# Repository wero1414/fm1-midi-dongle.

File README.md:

# FM-1 MIDI dongle

A small stick that plugs into the M-VAVE FM-1's USB-C port and gives it a **TRS MIDI OUT** and an
**isolated TRS MIDI IN**. The FM-1 is a USB MIDI device, so the dongle is a USB host built on the
WCH **CH32X035G8U6** (the cheapest WCH part with a full-speed USB host). It works with any FM-1 firmware
that sends MIDI over USB: Melodee, SLOOP, Felucca, Hortator, stock.

- `DESIGN.md`: the locked design, verified pins, open items, firmware plan, cost.
- `BOM.csv`: parts with LCSC numbers and a *Verified* column.
- `fm1-midi-dongle.kicad_sch` / `.kicad_pro`: KiCad 10 schematic (ERC clean). Generated by `tools/gen_sch.py`.
- `fm1-midi-dongle.kicad_pcb`: the board with placement only (generated by `tools/gen_pcb.py`); routing is manual.
- `fm1_dongle.kicad_sym`, `fm1_dongle.pretty`, `fm1_dongle.3dshapes`: project symbols and the exact LCSC footprints
  (from EasyEDA) for every IC and connector. `tools/export_jlc.sh` makes the JLCPCB BOM.

Status (2026-10-17): schematic done; PCB floorplanned (20 x 26 mm, 4 layers, 0.8 mm, placement DRC clean),
routing not started; firmware not started.

## Hardware summary
- USB-C male plug to the FM-1 (host side, 56 kΩ Rp on CC), VBUS through an SY6280AAC load switch set to 1 A.
- USB-C female for 5 V in only (5.1 kΩ Rd on CC1/CC2), no data.
- MIDI OUT: 3.3 V TRS type A (10 Ω tip, 33 Ω ring), PJ-320D jacks.
- MIDI IN: H11L1SM optocoupler, 220 Ω, 1N4148 reverse diode, TRS type A.
- Programming: WCH-LinkE on three bare pads (3V3 / PC18 DIO / GND), no connector.

## License
Hardware: CERN-OHL-P-2.0 (proposed; change if you prefer).

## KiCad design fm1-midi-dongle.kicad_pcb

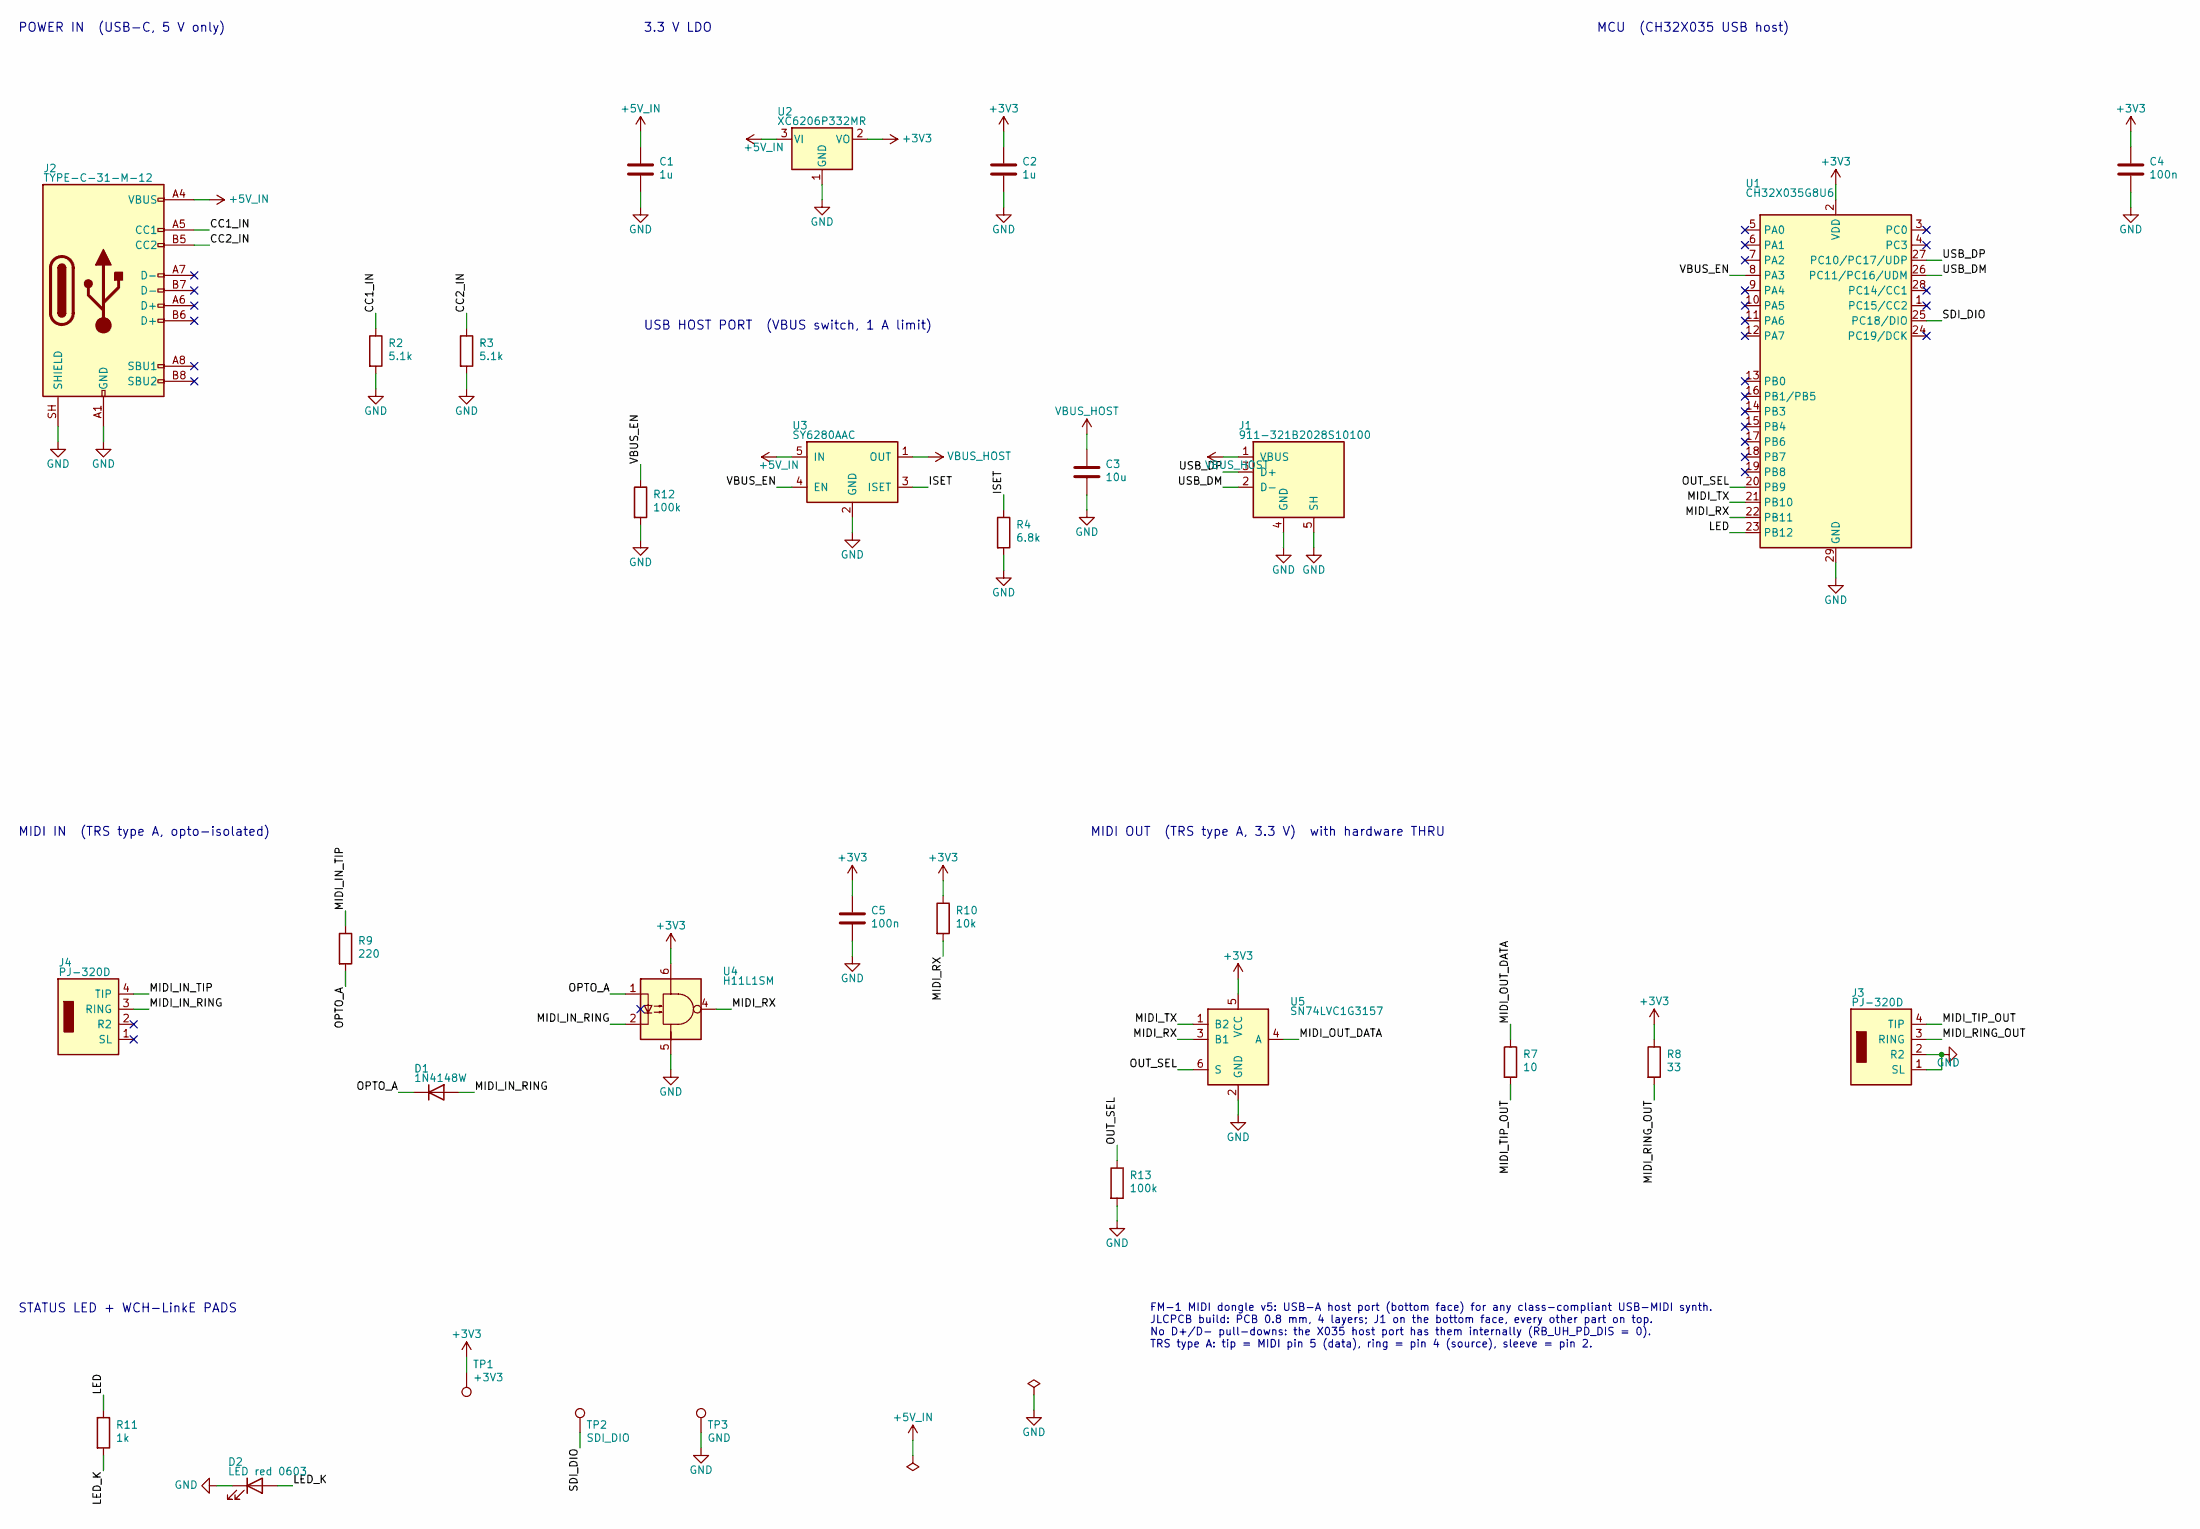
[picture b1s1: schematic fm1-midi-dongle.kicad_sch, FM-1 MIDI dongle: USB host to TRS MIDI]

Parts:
C1, C2: 1u; C_0603_1608Metric; MPN CL10A105KB8NNNC; LCSC# C15849
C3: 10u; C_0603_1608Metric; MPN CL10A106MA8NRNC; LCSC# C96446
C4, C5: 100n; C_0603_1608Metric; MPN CC0603KRX7R9BB104; LCSC# C14663
D1: 1N4148W; D_SOD-123; MPN 1N4148W; LCSC# C81598
D2: LED red 0603; LED_0603_1608Metric; MPN KT-0603R; LCSC# C2286
J1: 911-321B2028S10100; USB-A-SMD_911-321B2028S10100; MPN 911-321B2028S10100; LCSC# C42474
J2: TYPE-C-31-M-12; USB_C_Receptacle_HRO_TYPE-C-31-M-12; MPN TYPE-C-31-M-12; LCSC# C165948
J3, J4: PJ-320D; AUDIO-SMD_PJ-320D; MPN PJ-320D; LCSC# C521460
R2, R3: 5.1k; R_0603_1608Metric; MPN 0603WAF5101T5E; LCSC# C23186
R4: 6.8k; R_0603_1608Metric; MPN 0603WAF6801T5E; LCSC# C23212
R7: 10; R_0603_1608Metric; MPN 0603WAF100JT5E; LCSC# C22859
R8: 33; R_0603_1608Metric; MPN 0603WAF330JT5E; LCSC# C23140
R9: 220; R_0603_1608Metric; MPN 0603WAF2200T5E; LCSC# C22962
R10: 10k; R_0603_1608Metric; MPN 0603WAF1002T5E; LCSC# C25804
R11: 1k; R_0603_1608Metric; MPN 0603WAF1001T5E; LCSC# C21190
R12, R13: 100k; R_0603_1608Metric; MPN 0603WAF1003T5E; LCSC# C25803
TP1: +3V3; TestPoint_Pad_1.5x1.5mm
TP2: SDI_DIO; TestPoint_Pad_1.5x1.5mm
TP3: GND; TestPoint_Pad_1.5x1.5mm
U1: CH32X035G8U6; QFN-28_L4.0-W4.0-P0.40-BL-EP2.8; MPN CH32X035G8U6; LCSC# C7437027
U2: XC6206P332MR; SOT-23-3_L2.9-W1.6-P1.90-LS2.8-BR; MPN XC6206P332MR; LCSC# C5446
U3: SY6280AAC; SOT-23-5_L3.0-W1.7-P0.95-LS2.8-BL; MPN SY6280AAC; LCSC# C55136
U4: H11L1SM; SOP-6_L8.5-W6.4-P2.54-LS9.2-BL; MPN H11L1SM; LCSC# C899473
U5: SN74LVC1G3157; SOT-363_SC-70-6; MPN SN74LVC1G3157DCKR; LCSC# C38663

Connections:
+3V3: C2.1, C4.1, C5.1, R8.1, R10.1, TP1.1, U1.2 (VDD), U2.2 (VO), U4.6, U5.5 (VCC)
+5V_IN: C1.1, J2.A4 (VBUS), J2.A9 (VBUS), J2.B4 (VBUS), J2.B9 (VBUS), U2.3 (VI), U3.5 (IN)
/CC1_IN: J2.A5 (CC1), R2.1
/CC2_IN: J2.B5 (CC2), R3.1
/ISET: R4.1, U3.3 (ISET)
/LED: R11.1, U1.23 (PB12)
/LED_K: D2.2 (A), R11.2
/MIDI_IN_RING: D1.2 (A), J4.3 (RING), U4.2
/MIDI_IN_TIP: J4.4 (TIP), R9.1
/MIDI_OUT_DATA: R7.1, U5.4 (A)
/MIDI_RING_OUT: J3.3 (RING), R8.2
/MIDI_RX: R10.2, U1.22 (PB11), U4.4, U5.3 (B1)
/MIDI_TIP_OUT: J3.4 (TIP), R7.2
/MIDI_TX: U1.21 (PB10), U5.1 (B2)
/OPTO_A: D1.1 (K), R9.2, U4.1
/OUT_SEL: R13.1, U1.20 (PB9), U5.6 (S)
/SDI_DIO: TP2.1, U1.25 (PC18/DIO)
/USB_DM: J1.2 (D-), U1.26 (PC11/PC16/UDM)
/USB_DP: J1.3 (D+), U1.27 (PC10/PC17/UDP)
/VBUS_EN: R12.1, U1.8 (PA3), U3.4 (EN)
GND: C1.2, C2.2, C3.2, C4.2, C5.2, D2.1 (K), J1.4 (GND), J1.5 (SH), J1.6 (SH), J1.7 (SH), J1.8 (SH), J2.A1 (GND), J2.A12 (GND), J2.B1 (GND), J2.B12 (GND), J2.SH (SHIELD), J3.1 (SL), J3.2 (R2), R2.2, R3.2, R4.2, R12.2, R13.2, TP3.1, U1.29 (GND), U2.1 (GND), U3.2 (GND), U4.5, U5.2 (GND)
VBUS_HOST: C3.1, J1.1 (VBUS), U3.1 (OUT)

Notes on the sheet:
POWER IN (USB-C, 5 V only)
3.3 V LDO
USB HOST PORT (VBUS switch, 1 A limit)
MCU (CH32X035 USB host)
MIDI IN (TRS type A, opto-isolated)
MIDI OUT (TRS type A, 3.3 V) with hardware THRU
STATUS LED + WCH-LinkE PADS
FM-1 MIDI dongle v5: USB-A host port (bottom face) for any class-compliant USB-MIDI synth. JLCPCB build: PCB 0.8 mm, 4 layers; J1 on the bottom face, every other part on top. No D+/D- pull-downs: the X035 host port has them internally (RB_UH_PD_DIS = 0). TRS type A: tip = MIDI pin 5 (data), ring = 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

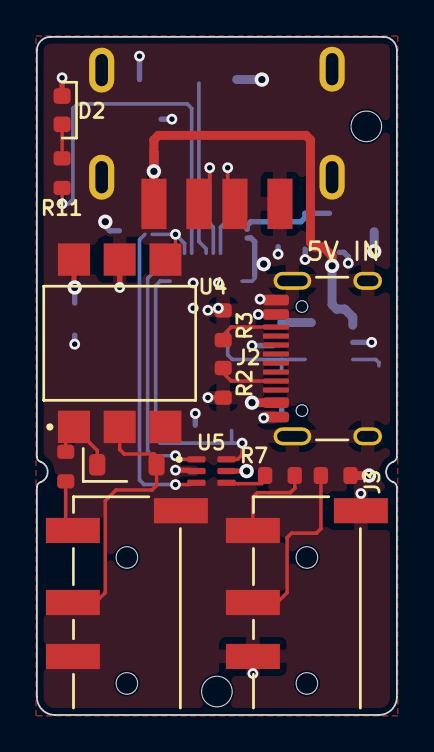
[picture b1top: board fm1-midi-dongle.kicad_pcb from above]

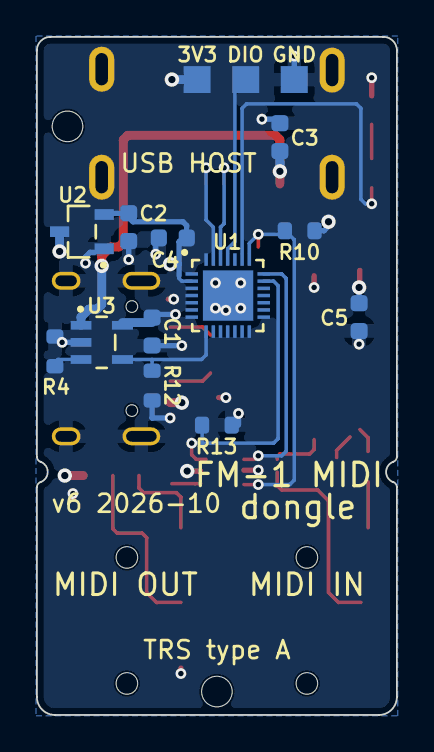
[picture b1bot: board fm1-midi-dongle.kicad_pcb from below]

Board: 4 copper layers, 20.0 x 37.7 mm, 31 parts (15 on the bottom side), 22 nets.

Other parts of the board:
H1, H2: M1.6 hole; MountingHole_1.7mm_NPTH

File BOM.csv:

Ref,Qty,Part,Value / note,Package,LCSC,JLCPCB tier,Price 1-10 (USD),Price 1k (USD),Verified
U1,1,CH32X035G8U6,RISC-V MCU with USB FS host; the TSSOP-20 F7P6 has NO host,QFN-28 4x4,C7437027,Extended,0.54,0.27,yes (datasheet V2.3 + LCSC + JLCPCB)
U2,1,XC6206P332MR,3.3 V LDO 200 mA,SOT-23-3,C5446,Basic,0.15,0.10,yes
U3,1,SY6280AAC,Host VBUS load switch; Ilim = 6800/Rset,SOT-23-5,C55136,Extended,0.09,0.06,yes (LCSC + datasheet)
U4,1,H11L1SM,MIDI IN optocoupler Schmitt output 3-16 V,SOP-6,C899473,Extended,0.68,0.33,yes
U5,1,SN74LVC1G3157DCKR (TI),Hardware MIDI THRU: SPDT switch feeding the OUT jack tip. v6: S low = B1 = opto output (THRU default via R13 pull-down); S high = B2 = MCU TX. Ron <= 25 ohm at 3 V,SC-70-6,C38663,Extended,0.075,0.048,2026-10-19: pinout + function table from TI SCES424O; price/stock 227k from the JLC parts DB snapshot (not re-fetched live)
J1,1,USB-A receptacle Jing Extension 911-321B2028S10100,host port for any class-compliant USB-MIDI synth; v6: mounted on the TOP face. 4 SMD signal pads + 4 through-hole shell legs (stick ~0.65 mm out of the 0.8 mm board),SMD + THT legs,C42474,Extended,0.058,0.037,2026-10-20: dimensions/pad layout from the datasheet drawing; footprint+3D from EasyEDA (3D offset corrected 3.74 mm); price/stock 17.7k from the JLC parts DB snapshot (not re-fetched live)
J2,1,USB-C female TYPE-C-31-M-12,5 V power in only,SMD 16P,C165948,Extended,0.17,0.10,yes
J3,1,PJ-320D (USAKRO),MIDI OUT 3.5 mm 4-pole SMD jack: 1 sleeve 2 ring2 3 ring1 4 tip; EasyEDA footprint; Economic assembly,SMD,C521460,Extended,0.11,0.066,verified 2026-10-17 (datasheet + KiCad PJ320D cross-check)
J4,1,PJ-320D (USAKRO),MIDI IN 3.5 mm 4-pole SMD jack (sleeve pins open),SMD,C521460,Extended,0.11,0.066,verified 2026-10-17
"R2,R3",2,Resistor,5.1k (Rd on J2 CC1 CC2: charger supplies 5 V),0603,C23186,Basic,,,verified 2026-10-17
R4,1,Resistor,6.8k (U3 ISET: 1 A limit),0603,C23212,Basic,,,verified 2026-10-17
R7,1,Resistor,10 Ω (MIDI OUT tip series),0603,C22859,Basic,,,verified 2026-10-17
R8,1,Resistor,33 Ω (MIDI OUT ring from 3V3),0603,C23140,Basic,,,verified 2026-10-17
R9,1,Resistor,220 Ω (MIDI IN LED series inside the loop; MIDI spec 220 Ω at 5 V),0603,C22962,Basic,,,verified 2026-10-17
R10,1,Resistor,10k (U4 output pull-up to 3V3),0603,C25804,Basic,,,verified 2026-10-17
R11,1,Resistor,1k (status LED),0603,C21190,Basic,,,verified 2026-10-17
D1,1,Diode,1N4148W (reverse protection across U4 LED),SOD-123,C81598,Basic,,,verified 2026-10-17
D2,1,LED red,status,0603,C2286,Basic,,,2026-10-18: C72043 (green) out of stock; owner chose Basic red KT-0603R, Vf 1.8-2.4 V, ~1.3 mA via R11 1k (JLC DB)
"C4,C5",2,Capacitor,100 nF 50 V X7R (U1 VDD / U4 VCC),0603,C14663,Basic,,,verified 2026-10-17
"C1,C2",2,Capacitor,1 µF 50 V X5R (LDO in / LDO out),0603,C15849,Basic,,,verified 2026-10-17 (page showed out of stock; re-check)
C3,1,Capacitor,10 µF 25 V X5R (VBUS_HOST bulk: a hot-plugged synth charges this instead of pulling the 5 V input down),0603,C96446,Basic,,,2026-10-20: Basic + 4.8M stock in the JLC parts DB snapshot (not re-fetched live)
"R12,R13",2,Resistor,100k (R12: U3 EN pull-down, VBUS off until firmware enables; R13: OUT_SEL pull-down (v6), hardware THRU until firmware drives PB9 high),0603,C25803,Basic,,,verified 2026-10-17
"TP1,TP2,TP3",3,Pad,SDI programming pads 1.5 mm (3V3 / DIO / GND) for WCH-LinkE wires,bare copper,none,,0,0,no part

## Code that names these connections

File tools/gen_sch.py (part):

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\t\t(symbol "SY6280AAC_1_1"
\t\t\t(pin power_out line (at 10.16 2.54 180) (length 2.54) (name "OUT" (effects (font (size 1.27 1.27)))) (number "1" (effects (font (size 1.27 1.27)))))
\t\t\t(pin power_in line (at 0 -7.62 90) (length 2.54) (name "GND" (effects (font (size 1.27 1.27)))) (number "2" (effects (font (size 1.27 1.27)))))
\t\t\t(pin passive line (at 10.16 -2.54 180) (length 2.54) (name "ISET" (effects (font (size 1.27 1.27)))) (number "3" (effects (font (size 1.27 1.27)))))
\t\t\t(pin input line (at -10.16 -2.54 0) (length 2.54) (name "EN" (effects (font (size 1.27 1.27)))) (number "4" (effects (font (size 1.27 1.27)))))
\t\t\t(pin power_in line (at -10.16 2.54 0) (length 2.54) (name "IN" (effects (font (size 1.27 1.27)))) (number "5" (effects (font (size 1.27 1.27)))))
\t\t)
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             '26': 'USB_DM', '27': 'USB_DP',
             '21': 'MIDI_TX', '22': 'MIDI_RX', '20': 'OUT_SEL',
             '25': 'SDI_DIO',
             '8': 'VBUS_EN', '23': 'LED'},    # v6: PA3 (pin 8) / PB12 (pin 23), datasheet V2.2 QFN28 drawing
            footprint='fm1_dongle:QFN-28_L4.0-W4.0-P0.40-BL-EP2.8', lcsc='C7437027',
            nc=('1', '3', '4', '5', '6', '7', '9', '10', '11', '12', '13', '14', '15', '16', '17', '18', '19', '24', '28'),
            extra=(('Note', 'QFN28 F7P6/TSSOP20 has NO USB host; G8U6 required. footprint from EasyEDA/LCSC for C7437027 (EP 2.8 mm).'),))
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    # ================= block 6: MIDI OUT with hardware THRU
    # U5 picks what drives the OUT jack's tip. OUT_SEL low (R13 pull-down default, MCU in reset or blank) = B1 =
    # MIDI_RX, the opto output: MIDI IN copied to MIDI OUT with no firmware. OUT_SEL high = B2 = MIDI_TX.
    # (v6: back to the v4 order; on the bottom face B2 and S line up with the MCU's TX and PB9 pins.)
    s.text('MIDI OUT  (TRS type A, 3.3 V)  with hardware THRU', 205, 160)
    s.place('fm1_dongle', 'SN74LVC1G3157', 'U5', 'SN74LVC1G3157', 230, 195,
            {'1': 'MIDI_TX', '3': 'MIDI_RX', '4': 'MIDI_OUT_DATA', '6': 'OUT_SEL', '5': '+3V3', '2': 'GND'},
            footprint='Package_TO_SOT_SMD:SOT-363_SC-70-6', lcsc='C38663',
            extra=(('Note', 'TI SCES424O: 1 B2, 2 GND, 3 B1, 4 A, 5 VCC, 6 S; S low A=B1, S high A=B2. Ron <= 25 ohm at 3 V'),))
    s.place('Device', 'R', 'R13', '100k', 210, 220, {'1': 'OUT_SEL', '2': 'GND'}, footprint=R, lcsc='C25803',
            extra=(('Note', 'OUT_SEL pull-down: default low = hardware THRU until firmware drives PB9 high'),))
    s.place('Device', 'R', 'R7', '10', 275, 200, {'1': 'MIDI_OUT_DATA', '2': 'MIDI_TIP_OUT'}, footprint=R, lcsc='C22859')
    s.place('Device', 'R', 'R8', '33', 300, 200, {'1': '+3V3', '2': 'MIDI_RING_OUT'}, footprint=R, lcsc='C23140')
    s.place('fm1_dongle', 'PJ-320D', 'J3', 'PJ-320D', 340, 195,
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    for ref, net, x in (('TP1', '+3V3', 100), ('TP2', 'SDI_DIO', 120), ('TP3', 'GND', 140)):
        s.place('Connector', 'TestPoint', ref, net, x, 262 if net != '+3V3' else 252, {'1': net}, rot=180 if net == '+3V3' else 0,
                footprint='TestPoint:TestPoint_Pad_1.5x1.5mm', in_bom=False,
                extra=(('Note', 'SDI pad: 3V3 / DIO (PC18, pin 25) / GND'),))

    # ================= power flags: the 5 V input and ground come from a connector, ERC needs a driver
    s.flag('+5V_IN', 175, 265)
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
